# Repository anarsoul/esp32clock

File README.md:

# onebitdawn

Open firmware for the HU-058 family of LED clock kits (HU-058 and
HU-058SE; the HU-058D should work too but is untested), with the kit's
8051 replaced by an ESP32-C3 on a small adapter board that takes the
8051's place in the DIP-16 footprint. Written in Rust with
[esp-hal](https://github.com/esp-rs/esp-hal) and Embassy.

It stands on [HU-058_ESPHome](https://github.com/misterblack1/HU-058_ESPHome)
by Adrian's Digital Basement (misterblack1), the original project,
which reverse-engineered the kit's display and its boards and put an
ESP32 with ESPHome in the 8051's place. Without that work this
project would not exist.

What the clock does:

- Time over NTP, 12 or 24 hour, in a timezone given as a POSIX TZ
  rule, so the clock follows daylight saving by itself.
- Alarm with a choice of melodies, per-weekday arming and a one-time
  skip.
- Nine colours and three brightness steps, from the buttons or the web
  pages.
- Room temperature and light level from the kit's NTC and LDR
  (optional), with the temperature on the panel once a minute.
- Web pages for the settings at `http://<ip>/` and a JSON API at
  `/api`.
- Home Assistant integration over MQTT with discovery, no YAML.
- Firmware updates over the LAN, two application slots with rollback.
- Setup from the clock's own access point, with a captive portal, when
  no network is stored.
- Self-healing: the clock resets itself when the network is lost for
  minutes or its firmware hangs (a watchdog), carrying the time and
  the alarm state across the reset.

The clock's pages, in the browser's light or dark; the manual has
all of them.

[`MANUAL.md`](MANUAL.md) is the manual: building the firmware from
source, updates, the buttons, the pages, the API and Home Assistant.
`ARCHITECTURE.md` is the overview of the firmware, `HISTORY.md` the
design record, `PLAN.md` what is still to do and `AGENTS.md` the
maintainer's guide.

## How it differs from the original

The kit's brain is an STC8G1K17, an 8051 with closed firmware. It
scans the display, reads the buttons and the sensors and drives the
buzzer; the time comes from a DS1302 and a coin cell, set with the
buttons (HU-058, HU-058SE), or from an ESP-01S that only passes the
time to the 8051 (HU-058D).

The original project,
[HU-058_ESPHome](https://github.com/misterblack1/HU-058_ESPHome),
replaced the 8051 with an ESP32-WROOM-32 running ESPHome, wired to
the socket's pins. This project starts from its documentation of the
display and differs in these ways:

- An ESP32-C3 module on an adapter board that goes in the 8051's
  footprint, so nothing is wired by hand.
- Its own firmware, in Rust, and not ESPHome: the clock keeps the time
  and its settings by itself and has its own web pages, and Home
  Assistant is optional.
- The display is scanned by hardware: SPI2 in quad mode used as a
  four-wire pattern generator, on one DMA transfer that loops for
  ever. The refresh is 7.1 kHz against about 400 Hz, with no flicker
  and nothing Wi-Fi can disturb.
- The buzzer, the thermometer and the light sensor are used: an alarm
  with melodies and [clips](#clips), and the room's readings.

## Hardware

### Parts

| part | notes |
| --- | --- |
| HU-058 or HU-058SE kit | the display half comes preassembled; the through-hole side is what you build. Sold on AliExpress as "DIY KIT Electronic Clock LED Microcontroller Soldering Exercise" (links in the [HU-058_ESPHome](https://github.com/misterblack1/HU-058_ESPHome) README). Get this one rather than the pricier HU-058D "ESP8266 IoT Colorful WiFi Clock Kit": the 8051 and the ESP-01S both go unused either way, and the D is untested here |
| ESP32-C3 module | an ESP32-C3 SuperMini **Plus**, the one with an antenna socket, with a small external antenna, is the one to get; a plain ESP32-C3 SuperMini or a Waveshare ESP32-C3-Zero works too, with weaker Wi-Fi. One adapter design for each footprint |
| adapter PCB | KiCad projects and gerbers in `adapter/adapter-esp32c3-zero` and `adapter/adapter-esp32c3-supermini`; two layers, 1.6 mm, any board house. The tested boards are `gerbers_clock_zero_v3.zip` and `gerbers_clock_supermini_v1.zip`; `gerbers_clock_zero_v4.zip` and `gerbers_clock_supermini_v2.zip` add the line output's filter and a header for an amplifier, and are ordered but not yet built or tested. Or order it from [PCBWay](https://www.pcbway.com/project/shareproject/esp32c3_adapter_for_HU_058_clock_e419ee2a.html), which supports this project |
| pin header | the one that comes with the module |
| 2 × 10 kΩ 0603 resistors, ideally 1 % | R1 and R2 on the adapter; only needed for the temperature and light sensors |
| 10 µF 25 V electrolytic capacitor | replaces the kit's C3, optional but recommended |
| 1N4148 diode, a 5.1 kΩ resistor | the buzzer mod: optional, but the clips do not sound good without it |
| 5 V USB power supply | 1 A recommended; 500 mA works |

### The clock board

Most of the kit stays in the bag.

**Fit these:**

| reference | part | why |
| --- | --- | --- |
| SW1, SW2 | 6 × 6 mm tactile switches | the two buttons |
| Q1 | S8550 PNP | buzzer driver |
| R5 | 10 kΩ, or 5.1 kΩ with the buzzer mod | base resistor of Q1 |
| LS1 | buzzer | the alarm |
| USB1 | micro USB | 5 V in |
| R4, R3 | NTC thermistor, LDR | optional: room temperature and light level |

**The sensors.** If you fit R3 and R4, also fit R1 and R2 on the
**adapter**. Do **not** fit the kit's own R1 and R2: they pull the
sensors up to 5 V, more than the ESP32-C3's inputs may see, where the
adapter's pull up to 3.3 V. Without the sensors, leave all four off;
the clock shows the time only.

**Replace C3**, a 0.1 µF ceramic on the 5 V rail next to the MCU
footprint, with a 10 µF 25 V electrolytic capacitor. Fit it last,
after the adapter is in place, since it stands in the way of soldering
the adapter. The negative lead goes towards the top of the board.

**Leave out everything else:** the STC8G1K17 (U4), the kit's R1 and
R2, header P3, and the timekeeping parts. On the HU-058 and HU-058SE
those are the DS1302 (U3), the crystal Y1 with C5 and C6, and the
CR1220 holder BT1; on the HU-058D the ESP-01S socket P5, the AMS1117
regulator U3 with C4 and C5, and R6 and R7. If you bought the kit
assembled, pull the 8051 and (on the HU-058D) the ESP-01S out of their
sockets before the adapter goes in.

**The DIP-16 socket is optional.** The adapter stands on the pin
header that comes with the module. If those pins fit the socket's
contacts and there is clearance under the adapter, fit the socket and
the adapter is removable; if not, solder the adapter's header straight
into the U4 footprint.

**The buzzer mod, optional:** two changes that make the alarm louder
and cleaner. The beeps and the note melodies are fine on a stock
board; the [clips](#clips) are not, so do the mod if you want them:
without it they are quiet and distorted. The firmware is the same
either way.

- A flyback diode, a 1N4148 will do, across the buzzer's two pins on
  the solder side: the cathode (the end with the band) to the pin Q1's
  collector drives, the buzzer's `+`, and the anode to the ground pin.
  Without it the buzzer's coil kicks that pin to 10 to 15 V below
  ground every time Q1 turns off.
- 5.1 kΩ for R5 instead of 10 kΩ, which doubles Q1's base current, so
  the transistor switches harder and the buzzer is louder.

A board with the mod. On the component side the 5.1 kΩ R5 is in its
place by the adapter. On the solder side the 1N4148 is across the
buzzer's two pins, in the corner by the buttons. The green on top of
the buzzer is masking tape over its opening, with a small hole made
by a needle, which makes a Helmholtz resonator of the buzzer's
cavity: not one of the two changes, but the tunes come through
louder.

With the mod Q1 gets hot to the touch while a clip of sampled sound, a
tracker module, a SID or a PT3 tune plays. Such a clip is a stream of
pulses 125 to 250 ns long, and the transistor cannot switch that
fast: with under a milliamp of base current its edges are no shorter
than the pulses. So for the length of the clip it never gets fully on
or off and sits in its linear region, half on, with the buzzer's mean
current through it: about 156 mA at 2.5 V at the worst, 0.4 W for the
buzzer's 16 Ω coil on 5 V, inside the S8550's rating of 0.625 W. It stays cold
when idle, on the beeps and on a beeper clip, whose pulses are long
enough to switch on. Q1 stands next to the NTC, so the firmware holds
the temperature at what it was before such a clip, for its length and
up to twenty minutes after.

[`speaker-mod/`](speaker-mod/README.md) describes a speaker in the
buzzer's place. Its base resistors, 330 Ω for R5 and 100 Ω from base
to emitter, drive Q1 hard enough to switch on every pulse, so with
that mod the transistor stays cool while a clip plays.

### The adapter

A two-layer board with the ESP32-C3 module on top, two 0603 pads (R1,
R2) and a DIP-16 footprint underneath for the module's pin header.
Build it in this order, since each step covers the pads of the next:

1. R1 and R2 (10 kΩ, 0603, ideally 1 %), if the clock board has the
   NTC and LDR.
2. The module. The antenna end hangs over a notch in the adapter's
   edge on purpose; do not let it sit over copper or over the clock
   board. With a SuperMini Plus, plug the external antenna into its
   socket and check that the module's antenna-select pad, where it has
   one, points at the socket.
3. The pin header, into the DIP-16 footprint, pins down.
4. Plug the adapter into the kit's socket, or solder its header into
   the U4 footprint. Pin 1 is the end marked on the clock board's
   silkscreen. Fit C3 on the clock board after this.

A module with a ceramic chip antenna normally works, but far from the
access point, or with the clock in its case on a shelf, the uplink
gets marginal: the access point hears the clock about 20 dB worse than
the clock hears it. An external antenna has been measured 25 to 30 dB
better than the chip antenna in the same spot.

Some ESP32-C3 SuperMini boards with the ceramic antenna need a lower
transmit power: at the default, 16 dBm, their antenna's mismatch makes
the link worse, not better, and the clock may fail to join its network
at all. The clock's own access point always transmits at a low power,
11 dBm, whatever the setting, so it can be reached either way. If the
clock does not connect to your network, hold both buttons for 10 s to
put it back into the access point, and choose a lower transmit power
on the setup form at `http://192.168.4.1/`; go down a step at a time
until it connects.

What the adapter connects:

| ESP32-C3 pin | socket pin | net | role |
| --- | --- | --- | --- |
| GPIO9 | 5 | DATA | driver 1 data |
| GPIO8 | 16 | CLK | driver 1 clock |
| GPIO7 | 2 | DATA_1 | driver 2 data |
| GPIO6 | 1 | CLK_1 | driver 2 clock |
| GPIO4 | 10 | S2 | upper button |
| GPIO3 | 9 | S1 | lower button |
| GPIO5 | 11 | R_B | buzzer, open-drain |
| GPIO0 | 3 | R_T | NTC divider, adapter R2 10 kΩ to 3V3 |
| GPIO1 | 4 | R_P | LDR divider, adapter R1 10 kΩ to 3V3 |
| 5V | 6 | +5V | supply |
| GND | 8 | GND | ground |

The HU-058D has driver 1's clock on socket pin 14 and not 16, so on a
D board a short wire from pin 14 to pin 16 should be needed. That
follows from the schematics; the HU-058D is untested.

### The lid

If the case needs more room, as for an adapter standing on its pin
header that no longer clears the original back lid, `lid/lid.scad` is
a parametric OpenSCAD model of a raised lid, for 3D printing. It has
the original's outline and takes the original screws; `raise` is how
much higher than the original it stands, 10 mm by default.

```sh
openscad -o lid.stl lid/lid.scad                    # raised by 10 mm
openscad -o lid.stl -D raise=6 lid/lid.scad         # or by another height
openscad -o lid.stl -D speaker=true lid/lid.scad    # with a socket for the speaker mod's speaker
```

`lid/lid-v2-printed.stl` is the 10 mm one as printed, which fits the
case.

### Power

Feed 5 V through the clock's own micro USB (USB1). A 1 A supply is
recommended; a 500 mA phone charger works. The firmware caps the drive
current at the 50 % brightness step by default; raising the cap on a
weak supply makes the board brown out when the brightness is stepped
up.

While the module is on USB for flashing, its 5 V pin feeds the clock
board, so the panel lights up on the bench. Do not power the clock
from USB1 and the module from its own USB at the same time.

### Firmware

No toolchain is needed: open the
[web installer](https://anarsoul.github.io/onebitdawn/) in Chrome or
Edge with the module on USB, pick a release and press Install. Or
build from source, with Rust 1.95 or newer and
[espflash](https://github.com/esp-rs/espflash) 4:

```sh
WIFI_SSID='home' WIFI_PASSWORD='…' TZ_RULE='PST8PDT,M3.2.0,M11.1.0' cargo run --release
```

A clock with no network stored starts as an access point: the panel
shows `AP`, the network is `clock-xxxx` with the password
`onebitdawn`, and the setup form is at `http://192.168.4.1/`. Holding
both buttons for 10 s gets there too. Everything after that, the
build's other variables and updates over the LAN included, is in
[`MANUAL.md`](MANUAL.md).

## Clips

The alarm melodies that are not notes are clips: sampled sound (PCM or
ADPCM), a ZX Spectrum beeper tune, FastTracker 2 modules, Commodore 64
SID tunes and ZX Spectrum AY tunes (Pro Tracker 3), the last three
played by the clock's own players and chip emulations. A clock's clips
are a clip pack in a flash partition of their own, so they can be
changed without a new firmware, from `http://<ip>/clips` or with
`scripts/clips.sh`. The default pack is the eight clips in `clips/`,
and the web installer writes it; a pack of your own tunes is made
[in the browser](https://anarsoul.github.io/onebitdawn/pack/) or with
the `onebitdawn-pack` command of a release. The default clips are made for a clock with
[the buzzer mod](#the-clock-board); a stock board plays them, but not
well.

The clips are other people's music and not under this project's
licence; [`clips/README.md`](clips/README.md) credits each. Making
clips and packs is in the manual's
[Clip packs](MANUAL.md#clip-packs).

## License

MIT or Apache-2.0, at your option. See `LICENSE-MIT` and
`LICENSE-APACHE`. A release's files are built from other people's
crates too; their licences are the release's
`onebitdawn-licenses-<tag>.txt` (`scripts/licenses.sh` makes it).

The display protocol and the board documentation come from
[misterblack1/HU-058_ESPHome](https://github.com/misterblack1/HU-058_ESPHome)
by Adrian's Digital Basement, the reverse-engineering project for
this kit, released as CC0. Its `docs/` directory has the AiP33628
protocol, the display map and the schematics of all three board
variants.

Much of this project, firmware and documentation alike, was written
with the assistance of an AI coding agent (Claude), working from the
design, the measurements on the panel and the review of the author.
Every change was built, run through the host tests and checked on the
hardware before it was kept, but read the code with that in mind, and
report what looks wrong.

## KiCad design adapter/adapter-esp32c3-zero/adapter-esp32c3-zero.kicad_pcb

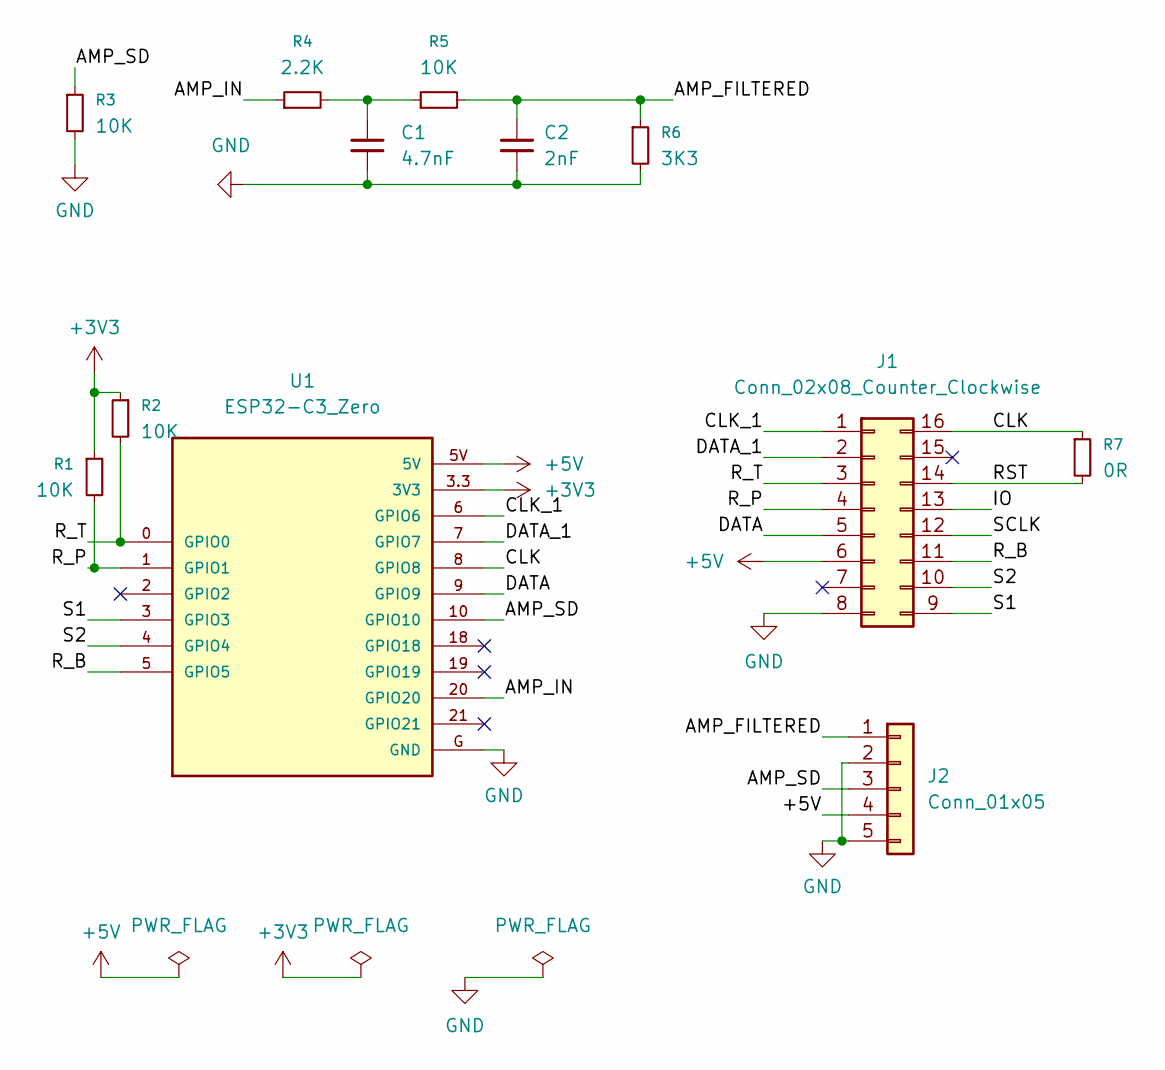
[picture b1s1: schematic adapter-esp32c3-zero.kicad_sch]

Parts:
C1: 4.7nF; C_0603_1608Metric_Pad1.08x0.95mm_HandSolder
C2: 2nF; C_0603_1608Metric_Pad1.08x0.95mm_HandSolder
J1: Conn_02x08_Counter_Clockwise; DIP-16_W7.62mm_Socket
J2: Conn_01x05; PinHeader_1x05_P2.54mm_Vertical
R1, R2, R3, R5: 10K; R_0603_1608Metric_Pad0.98x0.95mm_HandSolder
R4: 2.2K; R_0603_1608Metric_Pad0.98x0.95mm_HandSolder
R6: 3K3; R_0603_1608Metric_Pad0.98x0.95mm_HandSolder
R7: 0R; R_0603_1608Metric_Pad0.98x0.95mm_HandSolder
U1: ESP32-C3_Zero; MODULE_ESP32-C3_ZERO

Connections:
+3V3: R1.1, R2.1, U1.3.3 (3V3)
+5V: J1.6, J2.4, U1.5V
/AMP_FILTERED: C2.1, J2.1, R5.2, R6.1
/AMP_IN: R4.1, U1.20 (GPIO20)
/AMP_SD: J2.3, R3.1, U1.10 (GPIO10)
/CLK: J1.16, R7.1, U1.8 (GPIO8)
/CLK_1: J1.1, U1.6 (GPIO6)
/DATA: J1.5, U1.9 (GPIO9)
/DATA_1: J1.2, U1.7 (GPIO7)
/IO: J1.13
/RST: J1.14, R7.2
/R_B: J1.11, U1.5 (GPIO5)
/R_P: J1.4, R1.2, U1.1 (GPIO1)
/R_T: J1.3, R2.2, U1.0 (GPIO0)
/S1: J1.9, U1.3 (GPIO3)
/S2: J1.10, U1.4 (GPIO4)
/SCLK: J1.12
GND: C1.2, C2.2, J1.8, J2.2, J2.5, R3.2, R6.2, U1.G (GND)
unnamed: C1.1, R4.2, R5.1

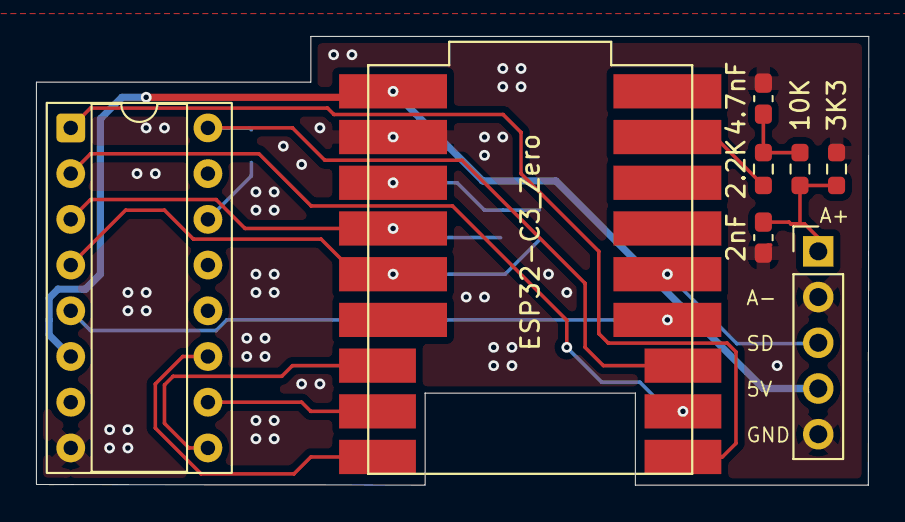
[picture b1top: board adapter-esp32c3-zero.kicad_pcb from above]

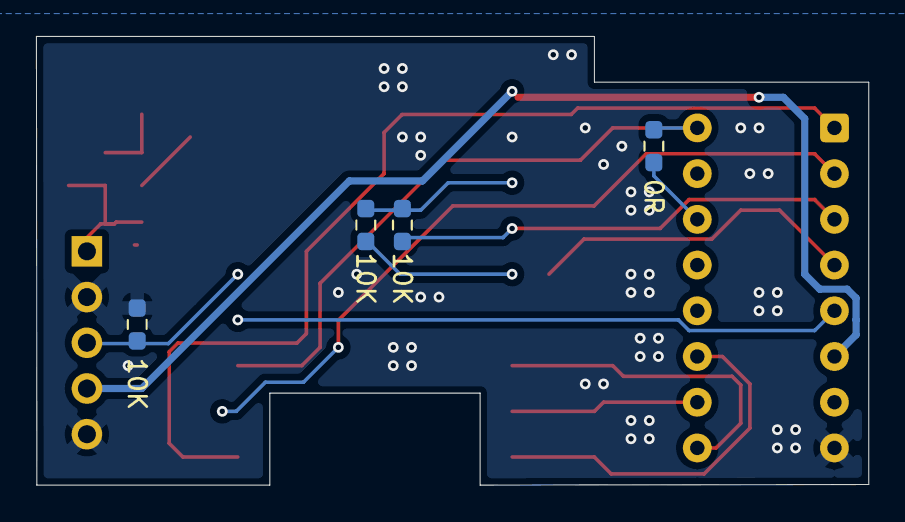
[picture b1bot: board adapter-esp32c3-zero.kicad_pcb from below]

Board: 2 copper layers, 46.2 x 24.9 mm, 12 parts (4 on the bottom side), 17 nets.

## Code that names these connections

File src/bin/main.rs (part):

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    // released (high impedance) is off, low is on.
    // Set the output register high and the pad open-drain now, so the
    // pin is released however the pad was left. The buzzer task takes
    // the pins over from here. The other is the line output, GPIO20,
    // for a clock with an amplifier: left as the ROM had it (UART0's
    // RX, an input) until the settings say it is in use, and with it
    // GPIO10, the shutdown pin of that amplifier.
    let mut sound_pins =
        buzzer::Pins::new(peripherals.GPIO5.degrade(), peripherals.GPIO20.degrade(), peripherals.GPIO10.degrade());
    sound_pins.rest(SoundPin::Buzzer);

    // Buttons switch to ground and the board has no pull-ups. GPIO4 is the
    // upper button on this board, GPIO3 the lower one.
    let button_top = Input::new(peripherals.GPIO4, InputConfig::default().with_pull(Pull::Up));
    let button_bottom = Input::new(peripherals.GPIO3, InputConfig::default().with_pull(Pull::Up));

    // Display wires, SPI2 SIO0 to SIO3. The scan task builds the bus from
    // them; see scan.rs and aip33628.rs.
    let wires = [
        display_wire(peripherals.GPIO9), // DATA,   driver 1
        display_wire(peripherals.GPIO8), // CLK,    driver 1
        display_wire(peripherals.GPIO7), // DATA_1, driver 2
        display_wire(peripherals.GPIO6), // CLK_1,  driver 2
    ];

    // Two transfer buffers: the one the ring points at, one being filled.
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    let clip_hw = clip::Hardware { i2s: peripherals.I2S0, dma: peripherals.DMA_CH1 };
    scan_spawner.spawn(clip::clip_task(clip_hw, clip_pins).expect("spawn clip"));
    spawner.spawn(buzzer::buzzer_task(Ledc::new(peripherals.LEDC), sound_pins).expect("spawn buzzer"));
    // The room sensors on the adapter: the NTC divider on GPIO0, the LDR
    // divider on GPIO1, both ADC1 (the converter that works with Wi-Fi on).
    let sensor_hw = sensors::SensorHardware { adc: peripherals.ADC1, ntc: peripherals.GPIO0, ldr: peripherals.GPIO1 };
    spawner.spawn(sensors::sensor_task(sensor_hw).expect("spawn sensors"));
    if let Some(store) = store.take() {
        spawner.spawn(storage::persist_task(store, stored).expect("spawn persist"));
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

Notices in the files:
src/bin/main.rs:
SPDX-License-Identifier: MIT OR Apache-2.0
Copyright (c) 2026 Vasily Khoruzhick
